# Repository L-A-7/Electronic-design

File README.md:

# Electronic design: workspace and roadmap

This workspace is for building a reliable, repeatable toolchain for PCB design. Each project
takes one step up in complexity, and each one has to be useful on its own.

## Layout

| Folder | Content |
|---|---|
| `projects/` | One folder per board: `docs/ hardware/ simulation/ firmware/ test/` |
| `library/` | Shared KiCad library (symbols, footprints, 3D models) for parts that aren't in the stock libs |
| `templates/` | KiCad project template (fab design rules, title block, net classes) |
| `tools/` | Scripts: ERC/DRC/fabrication exports through `kicad-cli`, simulation helpers |
| `learning/` | Notes and small exercises: [protocols](learning/protocols/README.md), [UV safety](learning/uv-safety.md), KiCad, circuit topics |
| `resources/` | Datasheets and application notes (stored locally, git-ignored if large) |
| `books/` | Reading notes |
| [`lab/`](lab/README.md) | Instrument inventory, purchase plan, measurement procedures |

## Toolchain

| Step | Tool | Status |
|---|---|---|
| Version control | git (one repo, one commit per meaningful design step) | initialised |
| Schematic / PCB | KiCad 9.0.8 | installed |
| Circuit simulation | ngspice inside the KiCad schematic editor (libngspice present); vendor SPICE models | available |
| Parameter sweeps | Python (`spicelib` or `PySpice`) driving ngspice | to do |
| Automated checks and exports | `tools/kicad-check.sh` (ERC, DRC, Gerbers, drill, BOM, position, PDF, STEP) | written |
| Mechanical fit | STEP export, then FreeCAD (installed) | available |
| Firmware | STM32CubeIDE / CubeMX on a **Nucleo** board until our own controller exists | to do |
| Protocol debugging | Logic analyser + sigrok/PulseView | to buy, see [`lab/`](lab/README.md) |
| Fabrication | JLCPCB / PCBWay (cheap PCBA) or Aisler (EU) | choose at milestone M4 |

## Roadmap

| # | Project | Main new skills | Useful because |
|---|---|---|---|
| 1 | **UV LED bench board** ([`projects/01-uv-bench`](projects/01-uv-bench/README.md)) | Power input protection, linear constant-current driver, photodiode TIA, **small STM32 on board** (control loop, I2C target, UART console), op-amp stability simulation, first full fab-and-test cycle | Self-regulating UV source: ask for a power, it holds it. Driven from a PC (USB-serial cable) now, from the main board over I2C later |
| 2 | *(optional, later)* **Small STM32 USB controller** ([`projects/02-usb-controller`](projects/02-usb-controller/README.md)) | STM32 minimum system, USB-C FS device, SWD, crystal, USB CDC firmware | Drives the UV bench from a PC. Proves the USB + STM32 layout cheaply before the large board |
| 3 | **Main STM32 board** ([`projects/03-main-board`](projects/03-main-board/README.md)) | USB-C PD power, stepper driver, 4 analogue acquisition channels, temperature, DACs, mixed-signal layout | The instrument controller |

Each project goes through the same milestones: **M0** toolchain, **M1** breadboard proof,
**M2** schematic and simulation, **M3** layout and review, **M4** fabrication, **M5** bring-up
and characterisation, **M6** firmware and documentation.

## Conventions

- Projects are numbered: `NN-short-name`.
- Hardware revisions are lettered (Rev A, Rev B). Tag them in git: `uv-bench-revA-fab`.
- Every design decision goes in the project `docs/` with its reasoning.
- Nothing goes to fabrication until `tools/kicad-check.sh` passes and the review checklist is done.

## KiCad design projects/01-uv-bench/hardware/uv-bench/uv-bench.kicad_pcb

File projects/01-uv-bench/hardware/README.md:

# UV bench: KiCad projects (Rev C + sensor head)

| Folder | Content |
|---|---|
| `uv-bench/` | The main board, KiCad 10: open `uv-bench/uv-bench.kicad_pro`. Rev C = Rev B + the remote-photodiode input J4 |
| `pd-head/` | The remote photodiode head (12 × 21 mm, SFH 2401 + 2 wire pads), its own project and Gerbers |
| `gen/` | The scripts that **generate** the schematic and the board: `design.py` (the circuit), `layout.py` (how the schematic is drawn), `placement.py` (where the parts go on the board). The head has its own three: `design_head.py`, `layout_head.py`, `placement_head.py` |
| `fab/` | The exact Gerbers sent to the board house, one folder per order (`2026-10-15-jlcpcb/`: Rev C + head, tag `uv-bench-revC-ordered`) |
| `archive/rev-a/` | Rev A (71 parts, 4 sheets), project + scripts as they were on 2026-10-13. Self-contained, for reference |

- How and why, block by block, plus the KiCad notes (§8): [`docs/rev-b-simple.md`](../docs/rev-b-simple.md).
- Generated parts list with nets: [`docs/parts-list.md`](../docs/parts-list.md).

## Regenerate (KiCad closed)

```bash
cd projects/01-uv-bench/hardware/gen
python3 gen_sch.py                                      # design.py + layout.py -> schematic (1 sheet), parts list, netlist check
~/Applications/kicad-10.0.7/bin/python3.11 gen_pcb.py   # netlist -> footprints, nets, placement
~/Applications/kicad-10.0.7/bin/python3.11 route.py     # Freerouting (~1 min), spur clean-up, GND pours, stitching vias
~/Applications/kicad-10.0.7/bin/python3.11 silk.py      # reference designators placed legibly
cd ../../../.. && tools/kicad-check.sh projects/01-uv-bench/hardware/uv-bench/uv-bench
```

**The sensor head** uses the same two generators, pointed at its own design module. It has two
hand-placed tracks, so no autorouter:

```bash
cd projects/01-uv-bench/hardware/gen
UVB_DESIGN=design_head python3 gen_sch.py
UVB_DESIGN=design_head ~/Applications/kicad-10.0.7/bin/python3.11 gen_pcb.py
cd ../../../.. && tools/kicad-check.sh projects/01-uv-bench/hardware/pd-head/pd-head
```

- **The autorouter isn't deterministic.** Each run gives a slightly different, equally valid
  routing. Always finish with `kicad-check.sh`.
- **Build a copy without touching the project:** set `UVB_PRJ=/some/dir/uv-bench` (a folder
  holding a copy of the `.kicad_pro`, `.kicad_dru` and lib tables). All scripts honour it.
- **Once you edit the PCB by hand, stop using `gen_pcb.py` and `route.py`.** They rebuild the
  board from scratch. From then on the schematic → PCB path is KiCad's *Update PCB from
  Schematic* (F8).

## Project settings (in `uv-bench.kicad_pro` / `.kicad_dru`)

| Item | Where in KiCad | Value |
|---|---|---|
| Board | Edge.Cuts | 58 × 32 mm, corners rounded R 3.5 mm (centred on the M3 holes), Ø 22 mm cut-out centred at (113, 116) for the LED star, 4 × M3 holes. Sensor head: 12 × 21 mm, R 1.5 mm |
| Design rules | Board Setup → Constraints | JLCPCB 2-layer standard with margin: 0.15 mm track/space, vias 0.6/0.3 mm, copper-to-edge 0.3 mm |
| Custom rules | Board Setup → Custom Rules | PTH annular ≥ 0.2 mm, silkscreen text ≥ 0.8 mm, **PD tracks ≥ 0.5 mm from PWM tracks** |
| Net classes | Board Setup → Net Classes | `Power` 0.5 mm (`+5V`, `LED_K`, `I_MON`); `Analog` (`PD`); `Noisy` (`PWM`, `UART_*`); Default 0.25 mm |
| Zones | F.Cu and B.Cu | GND pours + keepouts around the cut-out and along the edges |

**Never edit these files with a text editor or a script while KiCad has them open.**

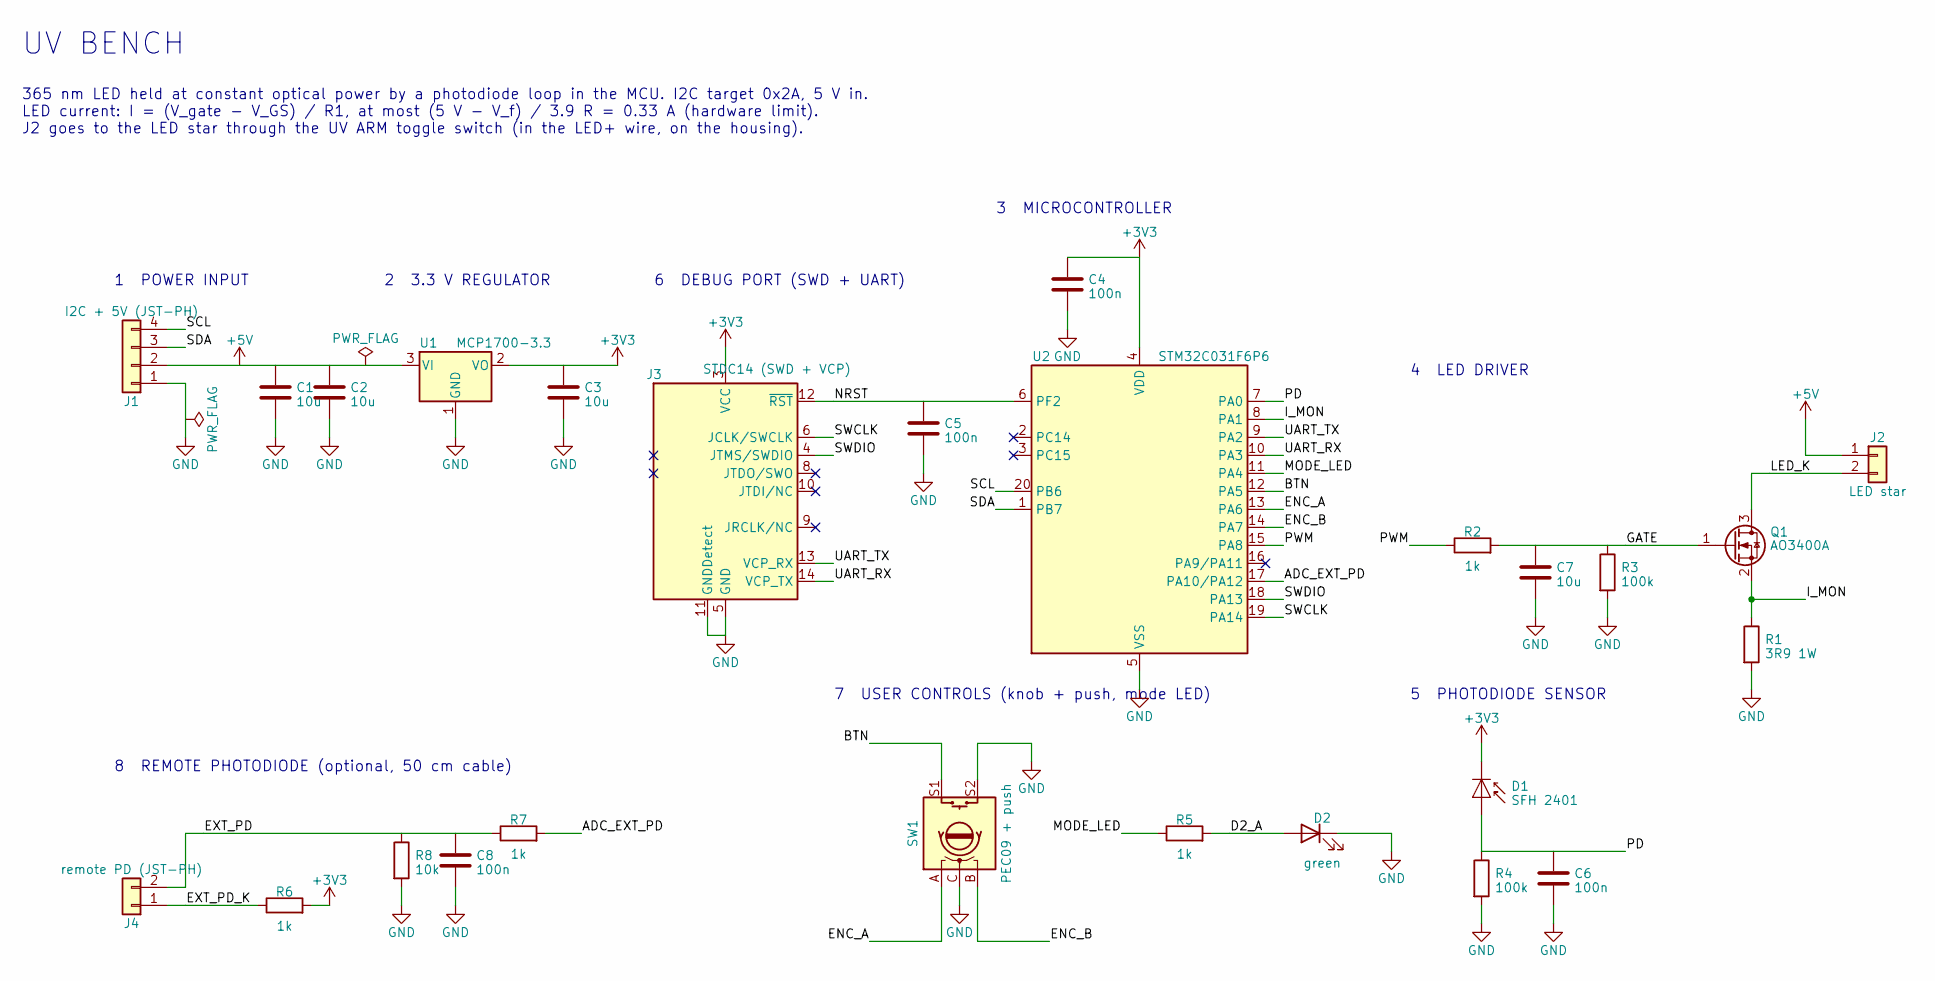
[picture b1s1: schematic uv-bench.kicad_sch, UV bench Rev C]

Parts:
C1, C2, C3, C7: 10u; C_0805_2012Metric_Pad1.18x1.45mm_HandSolder
C4, C5, C6, C8: 100n; C_0805_2012Metric_Pad1.18x1.45mm_HandSolder
D1: SFH 2401; Osram_BPW34S-SMD; MPN ams OSRAM SFH 2401
D2: green; LED_0805_2012Metric_Pad1.15x1.40mm_HandSolder
J1: I2C + 5V (JST-PH); JST_PH_B4B-PH-K_1x04_P2.00mm_Vertical; MPN JST B4B-PH-K-S
J2: LED star; SolderWire-0.25sqmm_1x02_P4.2mm_D0.65mm_OD1.7mm
J3: STDC14 (SWD + VCP); PinHeader_2x07_P1.27mm_Vertical_SMD; MPN Samtec FTSH-107-01-L-DV-K
J4: remote PD (JST-PH); JST_PH_B2B-PH-K_1x02_P2.00mm_Vertical; MPN JST B2B-PH-K-S
Q1: AO3400A; SOT-23_Handsoldering; MPN Alpha & Omega AO3400A
R1: 3R9 1W; R_2512_6332Metric_Pad1.40x3.35mm_HandSolder; MPN any 3.9 R 1 W 2512, e.g. Yageo RC2512FK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
R2, R5, R6, R7: 1k; R_0805_2012Metric_Pad1.20x1.40mm_HandSolder
R3, R4: 100k; R_0805_2012Metric_Pad1.20x1.40mm_HandSolder
R8: 10k; R_0805_2012Metric_Pad1.20x1.40mm_HandSolder
SW1: PEC09 + push; RotaryEncoder_Bourns_Horizontal_PEC09-2xxxF-Sxxxx; MPN Bourns PEC09-2xxxF-Sxxxx (with switch; 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
U1: MCP1700-3.3; SOT-23_Handsoldering; MPN Microchip MCP1700T-3302E/TT
U2: STM32C031F6P6; TSSOP-20_4.4x6.5mm_P0.65mm; MPN ST STM32C031F6P6

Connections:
+3V3: C3.1, C4.1, D1.1 (K), J3.3 (VCC), R6.2, U1.2 (VO), U2.4 (VDD)
+5V: C1.1, C2.1, J1.2, J2.1, U1.3 (VI)
/ADC_EXT_PD: R7.2, U2.17 (PA10/PA12)
/BTN: SW1.S1, U2.12 (PA5)
/D2_A: D2.2 (A), R5.2
/ENC_A: SW1.A, U2.13 (PA6)
/ENC_B: SW1.B, U2.14 (PA7)
/EXT_PD: C8.1, J4.2, R7.1, R8.1
/EXT_PD_K: J4.1, R6.1
/GATE: C7.1, Q1.1 (G), R2.2, R3.1
/I_MON: Q1.2 (S), R1.1, U2.8 (PA1)
/LED_K: J2.2, Q1.3 (D)
/MODE_LED: R5.1, U2.11 (PA4)
/NRST: C5.1, J3.12 (~RST), U2.6 (PF2)
/PD: C6.1, D1.2 (A), R4.1, U2.7 (PA0)
/PWM: R2.1, U2.15 (PA8)
/SCL: J1.4, U2.20 (PB6)
/SDA: J1.3, U2.1 (PB7)
/SWCLK: J3.6 (JCLK/SWCLK), U2.19 (PA14)
/SWDIO: J3.4 (JTMS/SWDIO), U2.18 (PA13)
/UART_RX: J3.14 (VCP_TX), U2.10 (PA3)
/UART_TX: J3.13 (VCP_RX), U2.9 (PA2)
GND: C1.2, C2.2, C3.2, C4.2, C5.2, C6.2, C7.2, C8.2, D2.1 (K), J1.1, J3.5 (GND), J3.7 (GND), J3.11 (GNDDetect), R1.2, R3.2, R4.2, R8.2, SW1.C, SW1.S2, U1.1 (GND), U2.5 (VSS)

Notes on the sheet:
UV BENCH
365 nm LED held at constant optical power by a photodiode loop in the MCU. I2C target 0x2A, 5 V in. LED current: I = (V_gate - V_GS) / R1, at most (5 V - V_f) / 3.9 R = 0.33 A (hardware limit). J2 goes to the LED star through the UV ARM toggle switch (in the LED+ wire, on the housing).
1 POWER INPUT
2 3.3 V REGULATOR
6 DEBUG PORT (SWD + UART)
3 MICROCONTROLLER
4 LED DRIVER
5 PHOTODIODE SENSOR
7 USER CONTROLS (knob + push, mode LED)
8 REMOTE PHOTODIODE (optional, 50 cm cable)

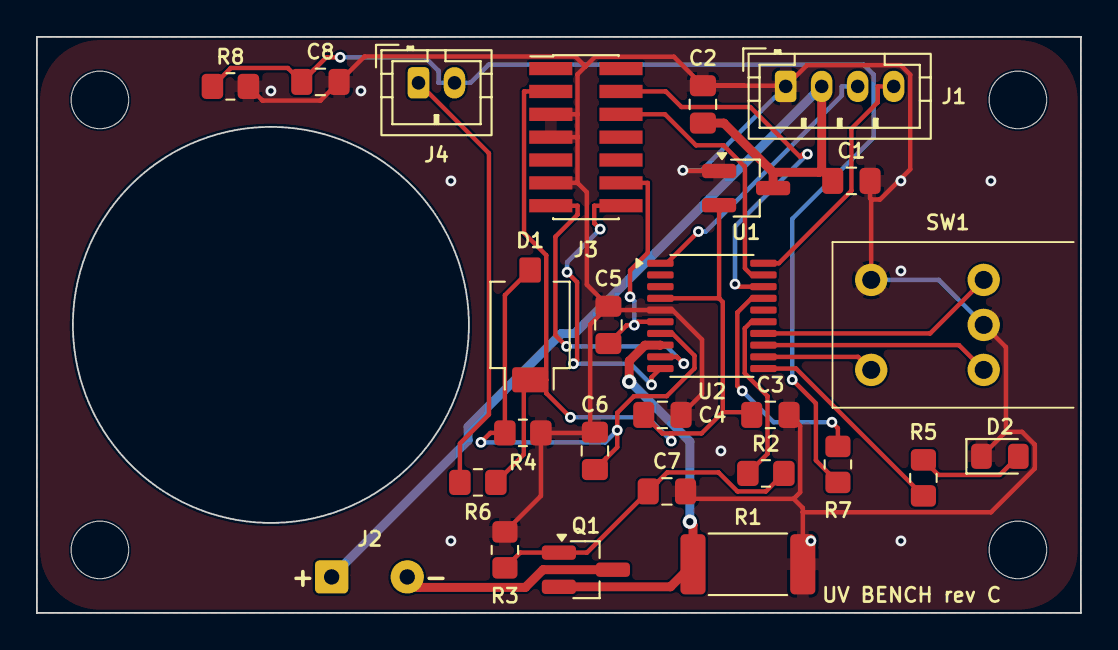
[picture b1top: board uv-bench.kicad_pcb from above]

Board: 2 copper layers, 58.0 x 32.0 mm, 30 parts (0 on the bottom side), 23 nets.

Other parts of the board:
H1, H2, H3, H4: MountingHole_3.2mm_M3

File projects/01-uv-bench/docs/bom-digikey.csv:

Quantity,Manufacturer,Manufacturer Part Number,Customer Reference
3,STMicroelectronics,STM32C031F6P6,U2 MCU
3,Microchip,MCP1702T-3302E/CB,U1 LDO 3.3V (MCP1700 out of stock)
3,Alpha & Omega Semiconductor,AO3400A,Q1 MOSFET
4,ams OSRAM,SFH 2401,D1 photodiode + remote head D1
5,Kingbright,APT2012SGC,D2 green LED 0805
2,Bourns,PEC09-2220F-S0012,SW1 encoder + push
3,Vishay Dale,CRCW25123R90FKEG,R1 3.9R 1W 2512
10,Murata,GRM21BR61E106KA73L,C1 C2 C3 C7 10uF 25V X5R 0805
10,Samsung,CL21B104KBCNNNC,C4 C5 C6 C8 100nF 50V X7R 0805
10,Yageo,RC0805FR-071KL,R2 R5 R6 R7 1k 0805
10,Yageo,RC0805FR-0710KL,R8 10k 0805 (remote PD load)
10,Yageo,RC0805FR-07100KL,R3 R4 100k 0805
3,JST,B4B-PH-K-S,J1 board connector
4,JST,PHR-4,J1 cable housing
3,JST,B2B-PH-K-S,J4 remote PD board connector
4,JST,PHR-2,J4 cable housing
10,JST,ASPHSPH24K305,J1 + J4 cable pre-crimped leads 12in
3,Samtec,FTSH-107-01-L-DV-K,J3 STDC14 debug header 14-pin keyed
2,CLIFF Electronic Components,CL170826BR,knob 6mm D shaft
1,E-Switch,100SP1T1B1M1QEH,UV ARM toggle switch solder lug 6.35mm hole
1,Chip Quik,SMD291NL,flux no-clean lead-free tack 5cc syringe
1,STMicroelectronics,STLINK-V3MINIE,debug probe

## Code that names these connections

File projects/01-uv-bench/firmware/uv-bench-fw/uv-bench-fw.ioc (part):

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Mcu.Name=STM32C031F(4-6)Px
Mcu.Package=TSSOP20
Mcu.UserName=STM32C031F6Px
PA0.Mode=IN0
PA0.Signal=ADC1_IN0
PA1.Mode=IN1
PA1.Signal=ADC1_IN1
PA11\ [PA9]__PA9\ [PA11].StandardMode=true
PA12\ [PA10]__PA10\ [PA12].StandardMode=true
PA13.Mode=Serial_Wire
PA13.Signal=DEBUG_SWDIO
PA14-BOOT0.Mode=Serial_Wire
PA14-BOOT0.Signal=DEBUG_SWCLK
PA4.Signal=GPIO_Output
PA5.Signal=GPXTI5
PA6.Signal=S_TIM3_CH1
PA7.Signal=S_TIM3_CH2
PA8.Signal=S_TIM1_CH1
PB6.Mode=I2C
PB6.Signal=I2C1_SCL
PB7.Mode=I2C
PB7.Signal=I2C1_SDA
RCC.HSE_VALUE=8000000
RCC.SYSCLKFreq_VALUE=12000000
board=custom

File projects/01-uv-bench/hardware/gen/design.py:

"""UV bench Rev B: the circuit as data (single source of truth).

Every component is one line: reference prefix, library symbol, value, footprint, pin→net map,
and optional fields (MPN, DNP, unit). The generator `gen_sch.py` turns this into the KiCad
schematic, `gen_pcb.py` into the board. Why each block and value: ../../docs/rev-b-simple.md.
Rev A (71 parts, 4 sheets) is kept in ../archive/rev-a/.

Net naming rules (they drive the net classes in uv-bench.kicad_pro):
  +5V, LED_K, I_MON  -> Power class (wide tracks: they carry the LED current)
  PD                 -> Analog class (kept away from power tracks)
  GND, +3V3, +5V     -> power symbols; everything else is a net label
"""

REV = "C"
PAPER = "A4"

FP_R = "Resistor_SMD:R_0805_2012Metric_Pad1.20x1.40mm_HandSolder"
FP_C = "Capacitor_SMD:C_0805_2012Metric_Pad1.18x1.45mm_HandSolder"

R = lambda v, a, b, **k: ("R", "Device:R", v, FP_R, {"1": a, "2": b}, k)
C = lambda v, a, b, **k: ("C", "Device:C", v, FP_C, {"1": a, "2": b}, k)
NC = None   # pin intentionally not connected (gets a no-connect flag)

SHEETS = []


def sheet(title, filename, note, parts):
    SHEETS.append(dict(title=title, file=filename, note=note, parts=parts))


# References are given explicitly (ref=...) so they match docs/rev-b-simple.md block by block.
sheet("UV bench", "uv-bench.kicad_sch",
      "365 nm LED held at constant optical power by a photodiode loop in the MCU. I2C target 0x2A, 5 V in.\n"
      "LED current: I = (V_gate - V_GS) / R1, at most (5 V - V_f) / 3.9 R = 0.33 A (hardware limit).\n"
      "J2 goes to the LED star through the UV ARM toggle switch (in the LED+ wire, on the housing).",
      [
    # --- 1 power input
    ("J", "Connector_Generic:Conn_01x04", "I2C + 5V (JST-PH)", "Connector_JST:JST_PH_B4B-PH-K_1x04_P2.00mm_Vertical",
     {"1": "GND", "2": "+5V", "3": "SDA", "4": "SCL"}, {"MPN": "JST B4B-PH-K-S", "ref": "J1"}),
    C("10u", "+5V", "GND", ref="C1"),
    C("10u", "+5V", "GND", ref="C2"),
    ("PWR", "power:PWR_FLAG", "PWR_FLAG", "", {"1": "+5V"}, {}),
    ("PWR", "power:PWR_FLAG", "PWR_FLAG", "", {"1": "GND"}, {}),
    # --- 2 3.3 V regulator
    ("U", "Regulator_Linear:MCP1700x-330xxTT", "MCP1700-3.3", "Package_TO_SOT_SMD:SOT-23_Handsoldering",
     {"1": "GND", "2": "+3V3", "3": "+5V"}, {"MPN": "Microchip MCP1700T-3302E/TT", "ref": "U1"}),
    C("10u", "+3V3", "GND", ref="C3"),
    # --- 3 microcontroller
    ("U", "MCU_ST_STM32C0:STM32C031F6Px", "STM32C031F6P6", "Package_SO:TSSOP-20_4.4x6.5mm_P0.65mm",
     {"4": "+3V3", "5": "GND", "6": "NRST", "7": "PD", "8": "I_MON", "15": "PWM", "18": "SWDIO", "19": "SWCLK",
      "20": "SCL", "1": "SDA",
      "11": "MODE_LED", "12": "BTN", "13": "ENC_A", "14": "ENC_B",
      "9": "UART_TX", "10": "UART_RX",               # PA2/PA3 = USART2, to the ST-LINK's virtual COM port
      "17": "ADC_EXT_PD",                            # PA12 = ADC1_IN12 (shares pin 17 with PA10): remote photodiode.
      "2": NC, "3": NC, "16": NC},                   #   Not PA11 (pin 16): that pin is next to the PWM (pin 15)
     {"MPN": "ST STM32C031F6P6", "ref": "U2"}),
    C("100n", "+3V3", "GND", ref="C4"),           # decoupling, right at VDD
    C("100n", "NRST", "GND", ref="C5"),
    # --- 4 LED driver
    R("1k", "PWM", "GATE", ref="R2"),             # PWM -> DC filter (with C7)
    C("10u", "GATE", "GND", ref="C7"),
    R("100k", "GATE", "GND", ref="R3"),           # safety pull-down
    ("Q", "Transistor_FET:AO3400A", "AO3400A", "Package_TO_SOT_SMD:SOT-23_Handsoldering",
     {"1": "GATE", "2": "I_MON", "3": "LED_K"}, {"MPN": "Alpha & Omega AO3400A", "ref": "Q1"}),
    ("R", "Device:R", "3R9 1W", "Resistor_SMD:R_2512_6332Metric_Pad1.40x3.35mm_HandSolder",
     {"1": "I_MON", "2": "GND"}, {"MPN": "any 3.9 R 1 W 2512, e.g. Yageo RC2512FK-073R9L", "ref": "R1"}),
    ("J", "Connector_Generic:Conn_01x02", "LED star", "Connector_Wire:SolderWire-0.25sqmm_1x02_P4.2mm_D0.65mm_OD1.7mm",
     {"1": "+5V", "2": "LED_K"}, {"in_bom": False, "ref": "J2"}),
    # --- 5 photodiode sensor
    # SFH 2401 = successor of the discontinued BPW 34 BS: same solder pads (large pad = cathode), same
    # ~15 % relative sensitivity at 365 nm, so the BPW34S footprint and R4 = 100 k are kept.
    ("D", "Sensor_Optical:BPW34-SMD", "SFH 2401", "OptoDevice:Osram_BPW34S-SMD", {"1": "+3V3", "2": "PD"},
     {"MPN": "ams OSRAM SFH 2401", "ref": "D1"}),
    R("100k", "PD", "GND", ref="R4"),
    C("100n", "PD", "GND", ref="C6"),
    # --- 7 user controls: knob (encoder + push) and mode LED. No pull-ups/filters: the MCU's internal
    #     pull-ups, the timer's encoder mode with its input filter, and firmware debouncing do it.
    ("SW", "Device:RotaryEncoder_Switch", "PEC09 + push", "Rotary_Encoder:RotaryEncoder_Bourns_Horizontal_PEC09-2xxxF-Sxxxx",
     {"A": "ENC_A", "B": "ENC_B", "C": "GND", "S1": "BTN", "S2": "GND"},
     {"MPN": "Bourns PEC09-2xxxF-Sxxxx (with switch; pick the shaft length)", "ref": "SW1"}),
    R("1k", "MODE_LED", "D2_A", ref="R5"),
    ("D", "Device:LED", "green", "LED_SMD:LED_0805_2012Metric_Pad1.15x1.40mm_HandSolder",
     {"1": "GND", "2": "D2_A"}, {"ref": "D2"}),
    # --- 8 remote photodiode (Rev C, optional): an SFH 2401 on a small head PCB at the end of a 50 cm
    #     twisted pair, lying on the target under the same ZWB2 filter as the lamp. It is a current source
    #     (~5.6 uA per mW/cm2 through the filter), so the load and the filter sit HERE, at the ADC:
    #     cable pickup goes into a low impedance. R8 = 10 k reads ~0.5-50 mW/cm2 (swap it after measuring).
    #     R6 limits the current if the cable shorts +3V3 to GND; R7 + C8 protect the ADC pin from ESD when
    #     plugging. Unplugged, R8 pulls the input to 0 V: the firmware sees "no sensor".
    ("J", "Connector_Generic:Conn_01x02", "remote PD (JST-PH)", "Connector_JST:JST_PH_B2B-PH-K_1x02_P2.00mm_Vertical",
     {"1": "EXT_PD_K", "2": "EXT_PD"}, {"MPN": "JST B2B-PH-K-S", "ref": "J4"}),
    R("1k", "EXT_PD_K", "+3V3", ref="R6"),        # photodiode bias, short-circuit limit
    R("10k", "EXT_PD", "GND", ref="R8"),          # load: V = I_photo x 10 k
    C("100n", "EXT_PD", "GND", ref="C8"),         # tau = 1 ms with R8; ESD charge sink at the connector
    R("1k", "EXT_PD", "ADC_EXT_PD", ref="R7"),    # series resistor into the ADC pin
    # --- 6 debug port: ST's 14-pin STDC14, the connector of the STLINK-V3MINIE's cable (keyed: it can't go in
    #     the wrong way). Pins 3-12 are the ARM 10-pin layout; 13-14 add a UART, seen on the PC as a COM port
    #     through the probe's USB. Directions are the probe's: VCP_RX (13) receives what the MCU sends (TX).
    #     Pins 1-2 are not connected inside the probe; JTAG-only pins (SWO, JRCLK, JTDI) don't exist on a Cortex-M0+.
    ("J", "Connector:Conn_ST_STDC14", "STDC14 (SWD + VCP)", "Connector_PinHeader_1.27mm:PinHeader_2x07_P1.27mm_Vertical_SMD",
     {"1": NC, "2": NC, "3": "+3V3", "4": "SWDIO", "5": "GND", "6": "SWCLK", "7": "GND", "8": NC, "9": NC,
      "10": NC, "11": "GND", "12": "NRST", "13": "UART_TX", "14": "UART_RX"},
     {"MPN": "Samtec FTSH-107-01-L-DV-K", "ref": "J3"}),
])
